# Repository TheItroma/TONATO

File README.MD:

I'll add the pcb files one day and make the case once the pcb's second prototype is made

This is a failed version that lead me to make the "keystrip" one

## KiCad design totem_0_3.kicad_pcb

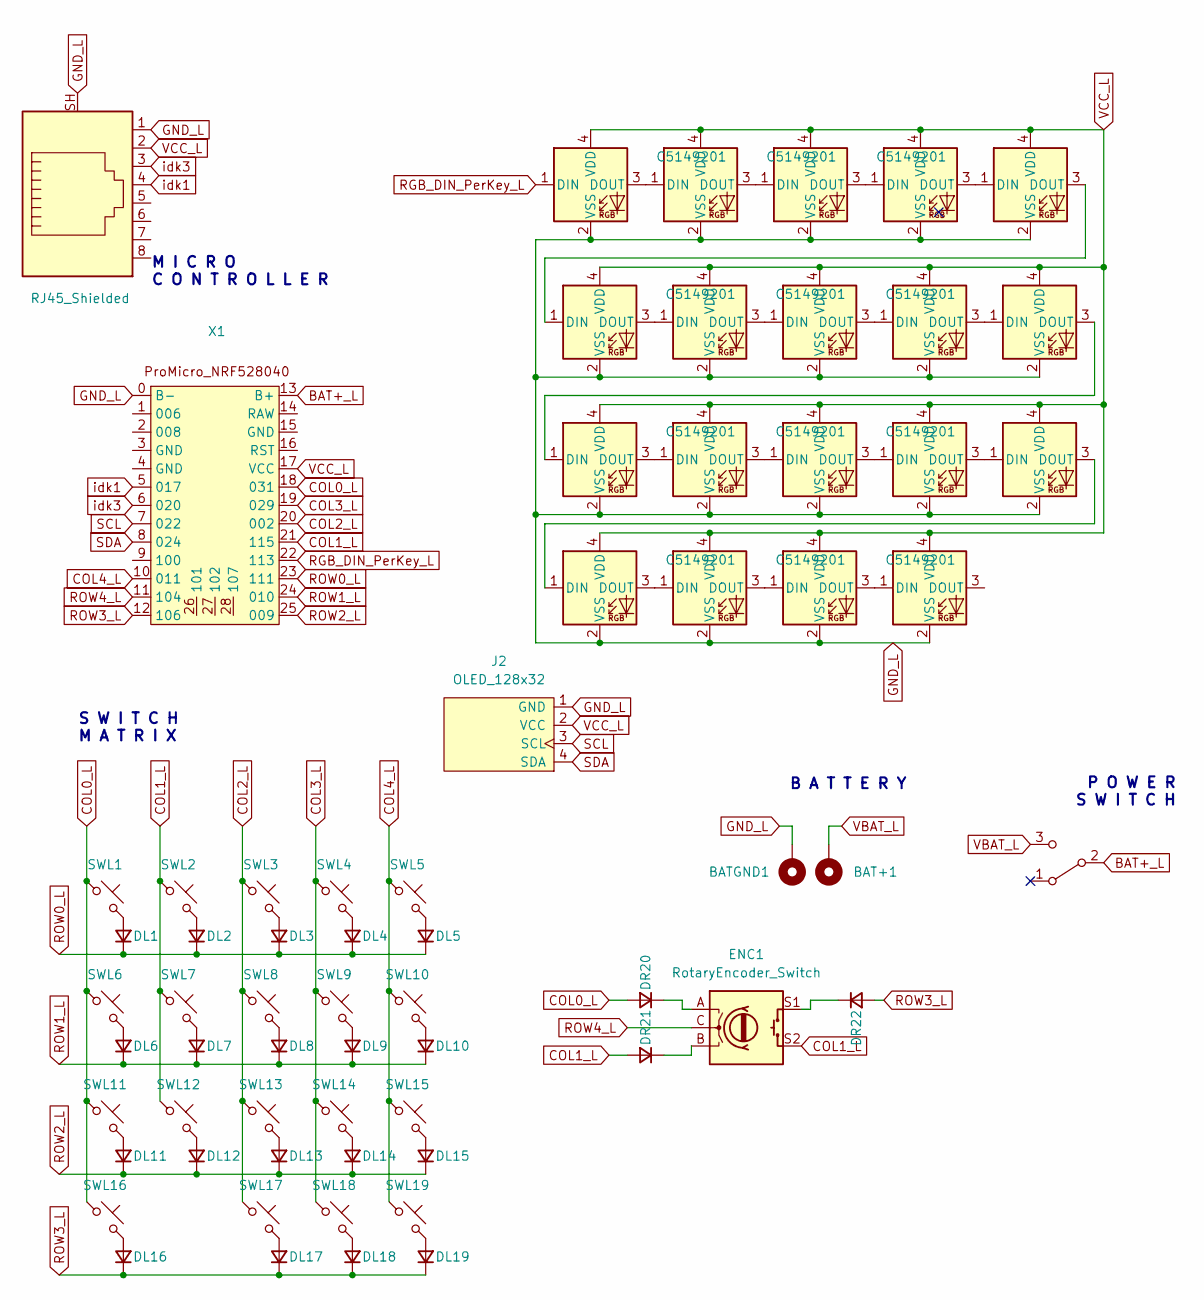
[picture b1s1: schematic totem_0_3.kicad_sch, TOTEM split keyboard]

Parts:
BAT+1: +; BatteryPad
BATGND1: -; BatteryPad
D4, D5, D6, D7, D8, D9, D10, D11, D12, D13, D14, D15, D16, D17, D18, D22, D23, D24, D25: LED_SK6812MINI; MX-1U-SK6812Mini-E; LCSC C5149201
DL1, DL2, DL3, DL4, DL5, DL6, DL7, DL8, DL9, DL10, DL11, DL12, DL13, DL14, DL15, DL16, DL17, DL18, DL19: D_Small; Dual-d
DR20, DR21, DR22: D_Small; Dual-d
ENC1: RotaryEncoder_Switch; EC11_Switch
J2: OLED_128x32
PSW1: SW_SPDT; Switch_MSK12C02_1
SWL1, SWL2, SWL3, SWL4, SWL5, SWL6, SWL7, SWL8, SWL9, SWL10, SWL11, SWL12, SWL13, SWL14, SWL15, SWL16, SWL17, SWL18, SWL19: SW_Push_45deg; MX-1U-Hotswap
U1: RJ45_Shielded; RJ45_Ninigi_GE_1
X1: ProMicro_NRF52840

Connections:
BAT+_L: PSW1.2 (B), X1.13 (B+)
COL0_L: DR20.2 (A), SWL1.1, SWL6.1, SWL11.1, SWL16.1, X1.18 (031)
COL1_L: DR21.2 (A), ENC1.S2, SWL2.1, SWL7.1, SWL12.1, X1.21 (115)
COL2_L: SWL3.1, SWL8.1, SWL13.1, SWL17.1, X1.20 (002)
COL3_L: SWL4.1, SWL9.1, SWL14.1, SWL18.1, X1.19 (029)
COL4_L: SWL5.1, SWL10.1, SWL15.1, SWL19.1, X1.10 (011)
GND_L: BATGND1.1, D4.2 (VSS), D5.2 (VSS), D6.2 (VSS), D7.2 (VSS), D8.2 (VSS), D9.2 (VSS), D10.2 (VSS), D11.2 (VSS), D12.2 (VSS), D13.2 (VSS), D14.2 (VSS), D15.2 (VSS), D16.2 (VSS), D17.2 (VSS), D18.2 (VSS), D22.2 (VSS), D23.2 (VSS), D24.2 (VSS), D25.2 (VSS), J2.1 (GND), U1.1, U1.SH, X1.0 (B-)
unnamed: D4.3 (DOUT), D5.1 (DIN)
unnamed: D5.3 (DOUT), D6.1 (DIN)
unnamed: D6.3 (DOUT), D7.1 (DIN)
unnamed: D7.3 (DOUT), D8.1 (DIN)
unnamed: D8.3 (DOUT), D9.1 (DIN)
unnamed: D9.3 (DOUT), D10.1 (DIN)
unnamed: D10.3 (DOUT), D11.1 (DIN)
unnamed: D11.3 (DOUT), D12.1 (DIN)
unnamed: D12.3 (DOUT), D13.1 (DIN)
unnamed: D13.3 (DOUT), D14.1 (DIN)
unnamed: D14.3 (DOUT), D15.1 (DIN)
unnamed: D15.3 (DOUT), D16.1 (DIN)
unnamed: D16.3 (DOUT), D17.1 (DIN)
unnamed: D17.3 (DOUT), D18.1 (DIN)
unnamed: D18.3 (DOUT), D22.1 (DIN)
unnamed: D22.3 (DOUT), D23.1 (DIN)
unnamed: D23.3 (DOUT), D24.1 (DIN)
unnamed: D24.3 (DOUT), D25.1 (DIN)
unnamed: DL1.2 (A), SWL1.2
unnamed: DL2.2 (A), SWL2.2
unnamed: DL3.2 (A), SWL3.2
unnamed: DL4.2 (A), SWL4.2
unnamed: DL5.2 (A), SWL5.2
unnamed: DL6.2 (A), SWL6.2
unnamed: DL7.2 (A), SWL7.2
unnamed: DL8.2 (A), SWL8.2
unnamed: DL9.2 (A), SWL9.2
unnamed: DL10.2 (A), SWL10.2
unnamed: DL11.2 (A), SWL11.2
unnamed: DL12.2 (A), SWL12.2
unnamed: DL13.2 (A), SWL13.2
unnamed: DL14.2 (A), SWL14.2
unnamed: DL15.2 (A), SWL15.2
unnamed: DL16.2 (A), SWL16.2
unnamed: DL17.2 (A), SWL17.2
unnamed: DL18.2 (A), SWL18.2
unnamed: DL19.2 (A), SWL19.2
unnamed: DR20.1 (K), ENC1.A
unnamed: DR21.1 (K), ENC1.B
unnamed: DR22.1 (K), ENC1.S1
RGB_DIN_PerKey_L: D4.1 (DIN), X1.22 (113)
ROW0_L: DL1.1 (K), DL2.1 (K), DL3.1 (K), DL4.1 (K), DL5.1 (K), X1.23 (111)
ROW1_L: DL6.1 (K), DL7.1 (K), DL8.1 (K), DL9.1 (K), DL10.1 (K), X1.24 (010)
ROW2_L: DL11.1 (K), DL12.1 (K), DL13.1 (K), DL14.1 (K), DL15.1 (K), X1.25 (009)
ROW3_L: DL16.1 (K), DL17.1 (K), DL18.1 (K), DL19.1 (K), DR22.2 (A), X1.12 (106)
ROW4_L: ENC1.C, X1.11 (104)
SCL: J2.3 (SCL), X1.7 (022)
SDA: J2.4 (SDA), X1.8 (024)
VBAT_L: BAT+1.1, PSW1.3 (C)
VCC_L: D4.4 (VDD), D5.4 (VDD), D6.4 (VDD), D7.4 (VDD), D8.4 (VDD), D9.4 (VDD), D10.4 (VDD), D11.4 (VDD), D12.4 (VDD), D13.4 (VDD), D14.4 (VDD), D15.4 (VDD), D16.4 (VDD), D17.4 (VDD), D18.4 (VDD), D22.4 (VDD), D23.4 (VDD), D24.4 (VDD), D25.4 (VDD), J2.2 (VCC), U1.2, U1.8, X1.17 (VCC)
idk1: U1.4, U1.6, X1.5 (017)
idk3: U1.3, U1.7, X1.6 (020)

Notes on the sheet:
S W I T C H M A T R I X
P O W E R S W I T C H
B A T T E R Y
M I C R O C O N T R O L L E R

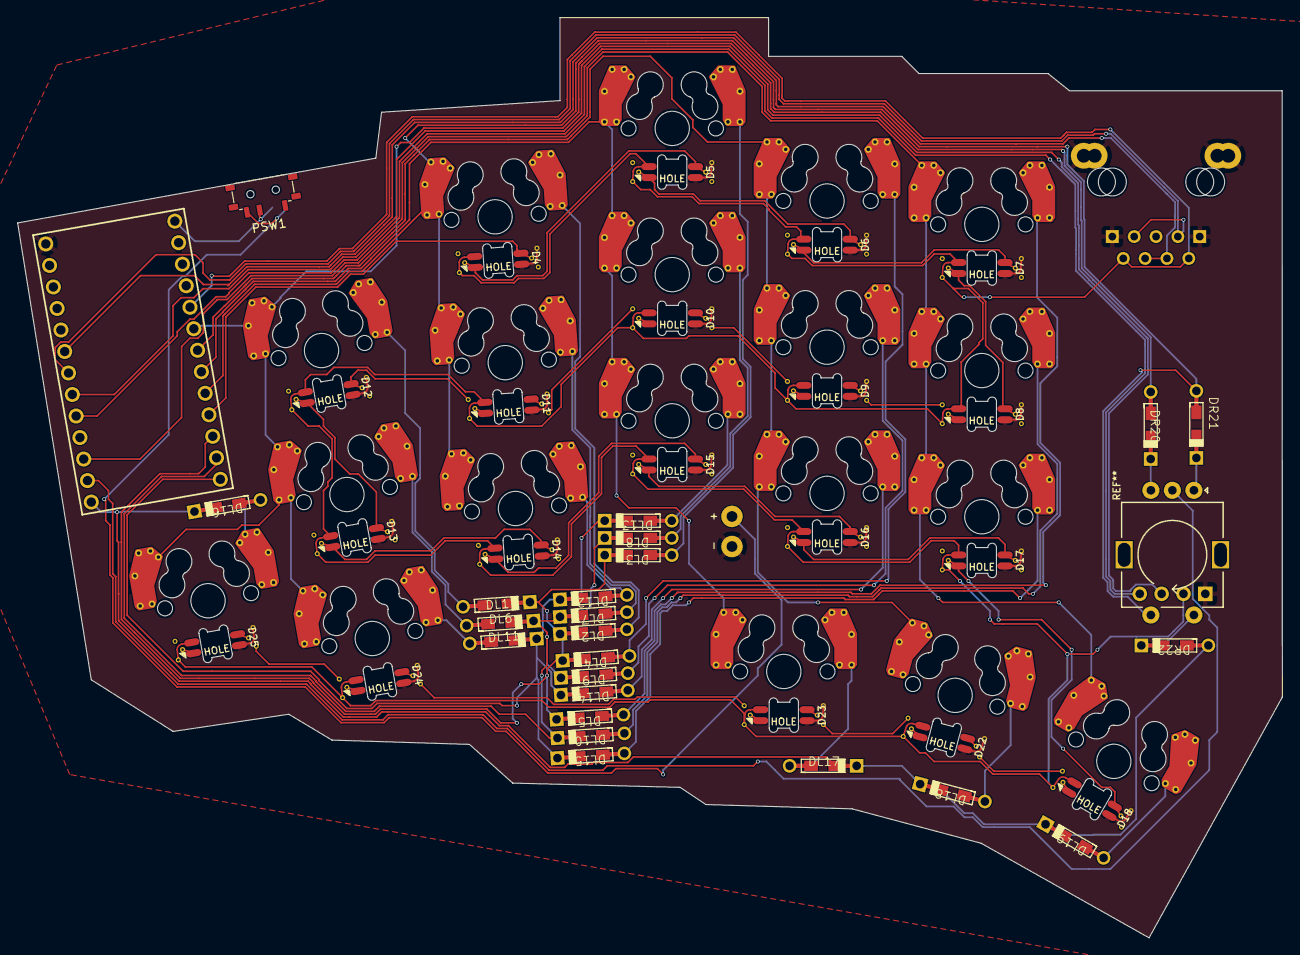
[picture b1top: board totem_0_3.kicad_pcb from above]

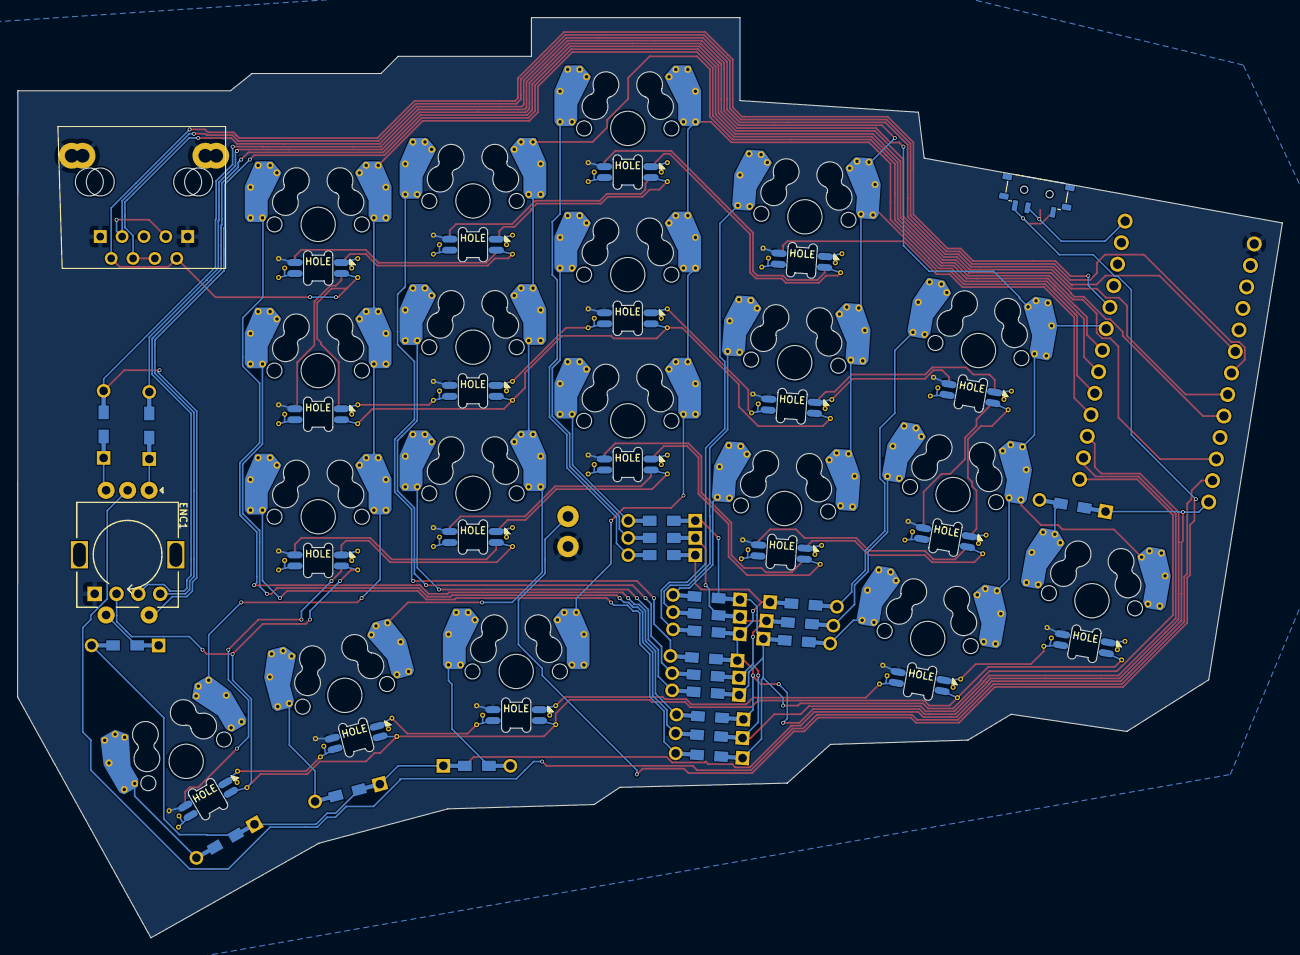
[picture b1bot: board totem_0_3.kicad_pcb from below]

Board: 2 copper layers, 147.1 x 107.0 mm, 67 parts (2 on the bottom side), 59 nets.

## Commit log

2025-08-20 gud day init
2026-05-17 finally uploading them
